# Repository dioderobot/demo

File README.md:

# Diode PCB boards

This repository contains schematics and boards built using the `pcb` command line utility by Diode, using the Zener language and open source compiler

## Prerequisites

For the most up to date information, visit our documentation at [`docs.pcb.new`](https://docs.pcb.new)

The open source PCB compiler is available at [`github.com/diodeinc/pcb`](https://github.com/diodeinc/pcb)

1. **KiCad 9.0**
   - Required for PCB layout
   - Download from [KiCad website](https://kicad.org/download)

## Project Structure

```
.
├── README.md
├── components              # Auto-generated component definitions (do not edit)
├── modules                 # User-authored reusable modules (.zen files)
├── boards                  # Board designs that use modules (.zen files)
└── pcb.toml               # Project configuration
```

## Usage Guidelines

### Building Projects
- Build your project using:
  ```bash
  pcb build
  ```

## Important Rules

1. **Dependencies**
   - Always use `pcb add` for dependencies
   - Never modify pcb.toml directly
   - Only add dependencies to directories with a `pcb.toml` file

2. **Best Practices**
   - Components in `components/` are auto-generated - never edit them manually
   - Create reusable modules in `modules/` directory
   - Board designs go in `boards/` directory
   - Use generic components for basic elements (capacitors, resistors, inductors)
   - Consult component datasheets when available

3. **Project Files**
   - Build artifacts are stored in `.pcb/` directory
   - Project configuration is in `pcb.toml`
   - Component files use `.zen` extension

## Zener Language Reference

Zener is a Starlark-based language for defining electronic components, modules, and boards as code. Starlark is a simplified dialect of Python designed for configuration files.

### Key Concepts

1. **Components** (in `components/` directory)
   - Auto-generated using `pcb search <PART_NUMBER>`
   - Never edit these manually
   - Stored as `.zen` files

2. **Modules** (in `modules/` directory)
   - User-authored reusable logic
   - Combine components and define connections
   - Named as `<module_name>.zen`

3. **Boards** (in `boards/` directory)
   - Instantiate modules for real-world use
   - Define the final PCB design
   - Named as `<board_name>.zen`

### Basic Syntax

Since Zener is based on Starlark, it follows Python-like syntax:
- Variables and functions follow Python conventions
- Comments use `#`
- Indentation matters
- No type annotations required

For detailed syntax and examples, refer to the [Diode PCB documentation](https://github.com/diodeinc/pcb)

## Component Management

Components are managed through the `pcb` command line tool:
- Use `pcb pro search <PART_NUMBER>` to find components
- Components are automatically downloaded and stored in `components/`
- Each component includes symbol, footprint, 3D model, and datasheet information

## Contributing

When contributing to this repository, please:
1. Follow the project structure
2. Use the provided tools for component and module creation
3. Ensure all components are properly documented
4. Test your changes with `pcb build`

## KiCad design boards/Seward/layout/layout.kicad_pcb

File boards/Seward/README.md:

# Seward

USB-C CMSIS-DAP v2 debug probe. STM32G0B1-based.

Drop-in replacement for a CMSIS-DAP v2 probe for flashing and debugging
Cortex-M targets. Target I/O rails auto-range over 1.8–5.0 V via
VTref-driven level shifters, so one probe covers every common target
voltage without jumpers or firmware switches. Exposes a keyed 10-pin
ARM Cortex-Debug header with bidirectional SWD and target-sourced SWO
capture presented to the host as a CDC-ACM virtual serial port.

## Highlights

- USB-C bus-powered, crystal-less (HSI48 + CRS), no PD negotiation
- STM32G0B1KBU6N (Cortex-M0+, UFQFPN-32 'N' pinout, 128 KB flash) —
  UCPD with internal dead-battery Rd, no external CC pulldowns
- Composite USB: CMSIS-DAP v2 (WinUSB, MS OS 2.0) + CDC-ACM for SWO;
  enumerates out of the box in `pyOCD` / `probe-rs` / `OpenOCD`
- Samtec FTSH-105 10-pin keyed ARM Cortex-Debug header (SWD + SWO)
- 1.8 V / 3.3 V / 5 V target support via 3× `SN74LXC1T45` level
  shifters driven by target VTref; firmware-controlled `SWD_DIR`
- nRESET driven directly from an FT_c (5 V tolerant) GPIO — no FET
  shifter, no body-diode back-feed path
- No probe-side back-feed when USB is unplugged (LXC1T45 Ioff + V₀₀
  disconnect, FT_c nRESET, no VTref buffer)
- Self-reflashable over USB DFU via BOOT0 button + USB cycle;
  Tag-Connect TC2030 SWD pads (unpopulated) for factory / recovery
- Three GPIO-driven status LEDs (STATUS green / DAP amber / SWO blue),
  no power-rail LED

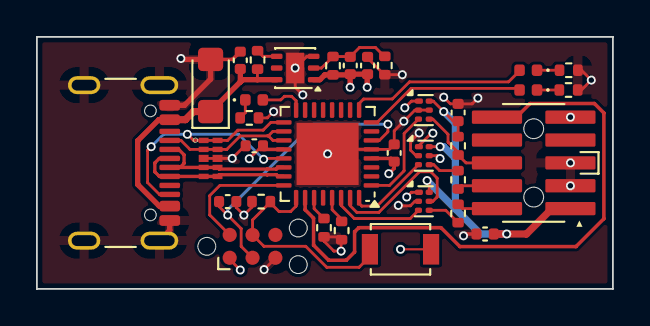
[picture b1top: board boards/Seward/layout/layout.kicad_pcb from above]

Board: 4 copper layers, 32.0 x 14.0 mm, 34 parts (0 on the bottom side), 31 nets.

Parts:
C1: GCM155R71H104KE02D; C_0402_1005Metric
C2, C3, C5, C6, C7, C8: GRM155Z71A105KE01D; C_0402_1005Metric
C4: GRM1555CYA103GE01D; C_0402_1005Metric
D1: LTST-C281KSKT; LED_0402_1005Metric
D2: VLMG1500-GS08; LED_0402_1005Metric
D3: VLMB1500-GS08; LED_0402_1005Metric
D4: SMF5V0A-E3; D_SMF
IC1: TPD4E05U06QDQARQ1; DQA_R-PUSON-N10_
J1: ?; Tag-Connect_TC2030-IDC-NL_2x03_P1.27mm_Vertical
J2: FTSH-105-01-L-DV-K-A-P-TR
J3: USB4105-GF-A; USB_C_Receptacle_GCT_USB4105-xx-A_16P_TopMnt_Horizontal
R1: ERJ-2RKF1002X; R_0402_1005Metric
R2, R3: ERJ-2RKF6800X; R_0402_1005Metric
R4, R5: ERJ-2RKF33R0X; R_0402_1005Metric
R6: ERJ-2RKF3300X; R_0402_1005Metric
R7, R8, R9, R10: ERJ-2RKF1003X; R_0402_1005Metric
R11: ERJ-2RKF5102X; R_0402_1005Metric
R12: ERJ-2RKF2553X; R_0402_1005Metric
SW1: B3U-1000P
U1: TPS74501PDRVR; TPS74x01P
U2, U3, U4: SN74LXC1T45DRYR; USON-6_1x1.45mm_P0.5mm
U5: STM32G0B1KBU6N; QFN-32-1EP_5x5mm_P0.5mm_EP3.45x3.45mm

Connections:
GND: C1.2, C2.2, C3.2, C5.2, C6.2, C7.2, C8.2, D4.2, IC1.3, IC1.8, J1.5, J2.3, J2.5, J2.9, J3.A1, J3.A12, J3.B1, J3.B12, J3.S1, R1.2, R2.2, R3.2, R6.2, R8.2, R9.2, R11.2, U1.3, U1.7, U2.2, U3.2, U4.2, U4.5, U5.5, U5.33
LED_DAP: D1.2, U5.8
LED_DAP_K: D1.1, R2.1
LED_STATUS: D2.2, U5.16
LED_STATUS_K: D2.1, R3.1
LED_SWO: D3.2, U5.9
LED_SWO_K: D3.1, R6.1
NRST: C1.1, J1.3, U5.6
SWD_A_SWCLK: U2.3, U5.32
SWD_A_SWDIO: U3.3, U5.30
SWD_B_SWCLK: J2.4, R4.2
SWD_B_SWDIO: J2.2, R5.2
SWD_DIR: U3.5, U5.31
SWD_LS_SWCLK: R4.1, U2.4
SWD_LS_SWDIO: R5.1, U3.4
SWD_SWCLK: J1.4, R1.1, SW1.1, U5.25
SWD_SWDIO: J1.2, U5.24
SWO_A: U4.3, U5.1
SWO_B: J2.6, R7.1, U4.4
TGT_NRESET: J2.10, U5.26
UCPD2_DBCC1: R8.1, U5.27
UCPD2_DBCC2: R9.1, U5.29
USB_C_CC1: IC1.2, IC1.9, J3.A5, U5.18, U5.19
USB_C_CC2: IC1.1, IC1.10, J3.B5, U5.17, U5.21
USB_C_D_N: IC1.4, IC1.7, J3.A7, J3.B7, U5.22
USB_C_D_P: IC1.5, IC1.6, J3.A6, J3.B6, U5.23
U_LDO.EN: R10.2, U1.4
U_LDO._FB: C4.2, R11.1, R12.2, U1.2
V3V3: C4.1, C6.1, C7.1, C8.1, J1.1, R12.1, SW1.2, U1.1, U2.1, U2.5, U3.1, U4.1, U5.4, U5.20
VBUS: C5.1, D4.1, J3.A4, J3.A9, J3.B4, J3.B9, R10.1, U1.6
VTREF: C2.1, C3.1, J2.1, R7.2, U2.6, U3.6, U4.6

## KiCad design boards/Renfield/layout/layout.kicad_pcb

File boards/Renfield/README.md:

# Renfield

USB-C PD sink dev board for STM32G0B1 UCPD firmware development.

The MCU runs the full PD sink stack itself — TCPP01-M12 is a
*protection* chip, not a PD controller. Plug into any USB-PD source,
negotiate a contract up to 20 V / 5 A, and pass the rail through a
firmware-gated OVP FET to a WAGO screw terminal.

## Highlights

- STM32G0B1KBU6N (Cortex-M0+, UFQFPN-32 'N' pinout, 128 KB flash)
- TCPP01-M12 + CSD17318Q2: hardware VBUS OVP @ 22 V, CC OVP @ 6 V,
  IEC 61000-4-2 L4 ESD on CC, connector-side dead-battery Rd
- Firmware-gated load rail (SSM3K15ACT shunt FET, default-off at
  reset) — firmware drives PA4 low to enable after PD contract
- Crystalless USB (HSI48 + CRS), USB-C data + CDC-ACM
- TPS70933 LDO from VBUS_RAW (always hot) → MCU survives OVP events
- WAGO 2060-452 push-in terminal for the negotiated rail
- Round Ø1.0 mm test pads: CC1/CC2 (connector-side, raw BMC), UART,
  scope trigger, OVP divider tap, GND
- Tag-Connect TC2030 SWD pads (no header populated — Cortex-M0+
  has no SWO)
- Four indicator LEDs (fault / contract / enum / heartbeat)

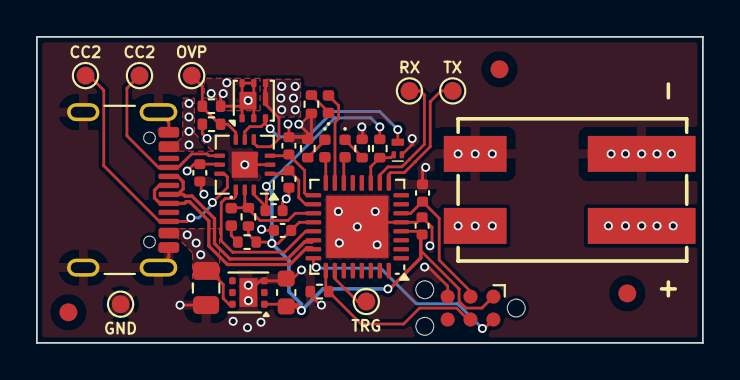
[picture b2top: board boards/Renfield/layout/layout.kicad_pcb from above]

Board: 4 copper layers, 37.0 x 17.0 mm, 41 parts (1 on the bottom side), 28 nets.

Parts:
C1, C2: GCM1555C1H221FA16D; C_0402_1005Metric
C3, C8, C9: GCM155R71H104KE02D; C_0402_1005Metric
C4: GRM21BZ71H475KE15K; C_0805_2012Metric
C5: GRM188Z71C475KE21D; C_0603_1608Metric
C6, C7: GRM155Z71A105KE01D; C_0402_1005Metric
D1: LTST-C281KSKT; LED_0402_1005Metric
D2, D4: VLMB1500-GS08; LED_0402_1005Metric
D3: VLMS1500-GS08; LED_0402_1005Metric
FID1, FID2, FID3: Fiducial; Fiducial_1mm_Mask2mm
J1: 2060-452/998-404; 2060-4xx_998-404-2P-white
J2: ?; Tag-Connect_TC2030-IDC-NL_2x03_P1.27mm_Vertical
J3: USB4105-GF-A; USB_C_Receptacle_GCT_USB4105-xx-A_16P_TopMnt_Horizontal
Q1: SSM3K15ACT,L3F; SSM3KxxxCT
Q2: CSD17318Q2; CSD1731xQ2
R1, R3: ERJ-2RKF1002X; R_0402_1005Metric
R2: ERJ-2RKF8200X; R_0402_1005Metric
R4, R6: ERJ-2RKF3900X; R_0402_1005Metric
R5: ERJ-2RKF4700X; R_0402_1005Metric
R7: ERJ-2RKF1003X; R_0402_1005Metric
R8: ERJ-2RKF1802X; R_0402_1005Metric
R9: ERJ-2RKF2943X; R_0402_1005Metric
TP1, TP2, TP3, TP4, TP5, TP6, TP7: ?; TestPoint_Pad_D1.0mm
U1: TPS70933QDRVRQ1; TPS709-Q1
U2: STM32G0B1KBU6N; QFN-32-1EP_5x5mm_P0.5mm_EP3.45x3.45mm
U3: TCPP01-M12; QFN-12-1EP_3x3mm_P0.5mm_EP1.45x1.45mm
V1: ?; version-footprint

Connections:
CC1_MCU: C1.1, U2.17, U3.3
CC2_MCU: C2.1, U2.18, U3.1
FET_GATE: Q1.3, Q2.3, U3.5
GND: C1.2, C2.2, C3.2, C4.2, C5.2, C6.2, C7.2, C8.2, C9.2, J1.2, J2.5, J3.A1, J3.A12, J3.B1, J3.B12, J3.S1, Q1.2, R1.2, R2.2, R4.2, R6.2, R8.2, TP3.1, U1.3, U1.7, U2.5, U2.33, U3.2, U3.13
HEARTBEAT_LED: D1.2, U2.15
LED_HEARTBEAT_K: D1.1, R2.1
LED_PD_CONTRACT_K: D2.1, R4.1
LED_TCPP01_FLT_A: D3.2, R5.2
LED_USB_ENUM_K: D4.1, R6.1
LOAD_EN_N: Q1.1, R3.2, U2.11
NRST: C3.1, J2.3, U2.6
OVP_SENSE: R8.1, R9.2, TP4.1, U3.6
PD_CONTRACT_LED: D2.2, U2.16
SCOPE_MARKER: TP5.1, U2.26
SWD_SWCLK: J2.4, R1.1, U2.25
SWD_SWDIO: J2.2, U2.24
TCPP01_DB: U2.21, U3.10
TCPP01_FLT: D3.1, R7.1, U2.19, U3.11
UART_RX: TP6.1, U2.10
UART_TX: TP7.1, U2.9
USB_C_CC1: J3.A5, TP1.1, U3.7
USB_C_CC2: J3.B5, TP2.1, U3.9
USB_C_D_N: J3.A7, J3.B7, U2.22
USB_C_D_P: J3.A6, J3.B6, U2.23
USB_ENUM_LED: D4.2, U2.14
V3V3: C5.1, C6.1, C7.1, C9.1, J2.1, R3.1, R5.1, R7.2, U1.1, U2.4, U2.20, U3.12
VBUS_PROT: J1.1, Q2.4, Q2.7, U3.4
VBUS_RAW: C4.1, C8.1, J3.A4, J3.A9, J3.B4, J3.B9, Q2.1, Q2.2, Q2.5, Q2.6, Q2.8, R9.1, U1.6, U3.8

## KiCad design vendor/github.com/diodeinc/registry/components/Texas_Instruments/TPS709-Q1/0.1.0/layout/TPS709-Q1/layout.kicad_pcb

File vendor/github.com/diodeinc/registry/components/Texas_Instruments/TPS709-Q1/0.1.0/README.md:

# TPS709-Q1 — TI 30 V, 150 mA low-Iq automotive LDO (WSON-6 / DRV)

Selector package for Texas Instruments' TPS709-Q1 AEC-Q100 linear
regulator family. All nine orderables share pinout, package, datasheet,
and performance — they differ only in the factory-trim output voltage.
Select by `output_voltage`; the matching silicon is picked automatically.

## Parts

| MPN | Vout | Max Dropout (150 mA) |
|-----|------|----------------------|
| TPS70912QDRVRQ1 | 1.2 V | — |
| TPS70915QDRVRQ1 | 1.5 V | — |
| TPS70918QDRVRQ1 | 1.8 V | — |
| TPS70925QDRVRQ1 | 2.5 V | — |
| TPS70927QDRVRQ1 | 2.7 V | — |
| TPS70928QDRVRQ1 | 2.8 V | — |
| TPS70930QDRVRQ1 | 3.0 V | 1.54 V |
| TPS70933QDRVRQ1 | 3.3 V | 1.54 V |
| TPS70950QDRVRQ1 | 5.0 V | 1.20 V |

All 9 share: 2.7–30 V Vin, 150 mA Iout, ~1 µA Iq, 80 dB PSRR at 10 Hz,
overcurrent / overtemperature / reverse-current / UVLO protection,
AEC-Q100 qualification.

## Selection

One config knob:

- `output_voltage` (Voltage) — factory-trim output. Must exactly match one
  of `"1.2V"`, `"1.5V"`, `"1.8V"`, `"2.5V"`, `"2.7V"`, `"2.8V"`, `"3V"`,
  `"3.3V"`, `"5V"`. Default: `"3.3V"`.

## Decoupling

Instantiated with the IC:

- `C_IN` — 4.7 µF / 50 V X7R / 0805. Sized for full 30 V Vin including
  automotive load-dump transients. Not required for stability per
  datasheet §7.1.1, but strongly recommended for ripple rejection.
- `C_OUT` — 4.7 µF / 16 V X7R / 0603. Meets the datasheet §7.1.1
  stability floor (≥ 2 µF effective for Vout < 1.5 V, ≥ 1.5 µF for
  Vout ≥ 1.5 V) across all 9 trims after tolerance + DC-bias derating.

## EN

Exposed as an optional `io(Net, ...)` with a default `NotConnected()` —
the datasheet explicitly allows EN to float (internal pull-up enables the
device). If driving externally, keep V_EN ≤ 6.5 V — do not tie EN to VIN
if VIN can exceed 6.5 V.

## Example

```zen
TPS709_Q1 = Module("@github/diodeinc/registry/components/Texas_Instruments/TPS709-Q1/TPS709-Q1.zen")

# Default 3.3 V (TPS70933QDRVRQ1)
TPS709_Q1(name="U_3V3", VIN=VBAT, VOUT=V3V3, GND=GND)

# Explicit 5 V rail, EN driven by an MCU GPIO (must be ≤ 6.5 V)
TPS709_Q1(
    name="U_5V",
    output_voltage="5V",
    VIN=VBAT,
    VOUT=V5,
    GND=GND,
    EN=SYS_EN,
)
```

## Package

**DRV / WSON-6** — 2 × 2 × 0.8 mm, 6-pin leadless DFN with exposed thermal
pad. Footprint is KiCad's stock `WSON-6-1EP_2x2mm_P0.65mm_EP1x1.6mm`
(IPC-7351 nominal density); electrically equivalent to TI's recommended
DRV land pattern. STEP 3D model is the KiCad-bundled file, embedded in
the `.kicad_mod` for self-contained use.

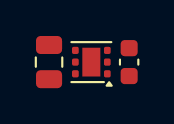
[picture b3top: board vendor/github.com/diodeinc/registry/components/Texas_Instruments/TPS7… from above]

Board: 2 copper layers, 3 parts (0 on the bottom side), 3 nets, no tracks yet.

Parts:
C1: GRM21BZ71H475KE15K; C_0805_2012Metric
C2: GRM188Z71C475KE21D; C_0603_1608Metric
U1: TPS70933QDRVRQ1; TPS709-Q1

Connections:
GND: C1.2, C2.2, U1.3, U1.7
VIN: C1.1, U1.6
VOUT: C2.1, U1.1

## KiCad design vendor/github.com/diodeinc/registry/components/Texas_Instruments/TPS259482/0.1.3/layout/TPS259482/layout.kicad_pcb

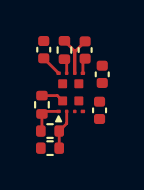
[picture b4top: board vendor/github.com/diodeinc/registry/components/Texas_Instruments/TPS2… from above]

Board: 2 copper layers, 9 parts (0 on the bottom side), 8 nets.

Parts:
C1: GCM1555C1H102FA16D; C_0402_1005Metric
C2, C4: GCM155R71H104KE02D; C_0402_1005Metric
C3: GRM1555CYA103GE01D; C_0402_1005Metric
R1: ERJ-2RKF3923X; R_0402_1005Metric
R2: ERJ-2RKF2672X; R_0402_1005Metric
R3: ERJ-2RKF7152X; R_0402_1005Metric
R4: ERJ-2RKF9760X; R_0402_1005Metric
U1: TPS259482AYWPR; TPS259482

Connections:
DVDT: C1.1, U1.7
EN: R1.2, R3.1, U1.1
GND: C1.2, C2.2, C3.2, C4.2, R2.2, R4.2, U1.8
ILM_MON: R4.1, U1.9
ITIMER: C3.1, U1.10
OVLO: R2.1, R3.2, U1.2
VIN: C2.1, R1.1, U1.5, U1.12
VOUT: C4.1, U1.6, U1.11

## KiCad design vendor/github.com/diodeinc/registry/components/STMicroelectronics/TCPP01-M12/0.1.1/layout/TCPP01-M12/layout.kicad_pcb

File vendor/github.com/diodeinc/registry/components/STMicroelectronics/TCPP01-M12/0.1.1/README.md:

# TCPP01-M12

STMicroelectronics USB Type-C port protection IC for sink applications. Provides
ESD, short-to-VBUS OVP on CC1/CC2, programmable VBUS OVP via an external
N-MOSFET, dead-battery management, and open-drain fault reporting in a 3 × 3 mm
QFN-12L.

The package ships a minimal reference circuit around the IC (VCC decoupling,
IN_GD ESD shunt, VBUS_CTRL divider, FLT pull-up). Use-case-specific parts
(external N-MOSFET, DB/ network, CC EMI caps, VBUS bulk/TVS) are still the
integrator's responsibility — see the `.zen` docstring.

## Usage

```python
TCPP01_M12 = Module("@github/diodeinc/registry/components/STMicroelectronics/TCPP01-M12/TCPP01-M12.zen")

TCPP01_M12(
    name="U1",
    VCC=vcc_3v3,
    GND=gnd,
    # Connector side
    CC1C=usb_cc1,
    CC2C=usb_cc2,
    IN_GD=usb_vbus,
    # System side
    CC1=mcu_cc1,
    CC2=mcu_cc2,
    SOURCE=sys_vbus,
    GATE=fet_gate,
    VBUS_CTRL=ovp_set,
    DB=dead_batt,
    FLT=fault_n,
    # Optional: override VBUS OVP trip (default 22 V for full PD range).
    # Use ~6 V for 5 V-only sinks.
    # vbus_ovp_threshold=Voltage("6V"),
)
```

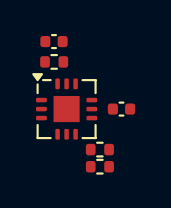
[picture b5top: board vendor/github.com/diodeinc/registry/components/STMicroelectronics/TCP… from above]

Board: 2 copper layers, 6 parts (0 on the bottom side), 5 nets, no tracks yet.

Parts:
C1, C2: GCM155R71H104KE02D; C_0402_1005Metric
R1: ERJ-2RKF1003X; R_0402_1005Metric
R2: ERJ-2RKF1802X; R_0402_1005Metric
R3: ERJ-2RKF2943X; R_0402_1005Metric
U1: TCPP01-M12; QFN-12-1EP_3x3mm_P0.5mm_EP1.45x1.45mm

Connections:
FLT: R1.1, U1.11
GND: C1.2, C2.2, R2.2, U1.2, U1.13
IN_GD: C1.1, R3.1, U1.8
VBUS_CTRL: R2.1, R3.2, U1.6
VCC: C2.1, R1.2, U1.12

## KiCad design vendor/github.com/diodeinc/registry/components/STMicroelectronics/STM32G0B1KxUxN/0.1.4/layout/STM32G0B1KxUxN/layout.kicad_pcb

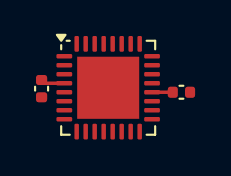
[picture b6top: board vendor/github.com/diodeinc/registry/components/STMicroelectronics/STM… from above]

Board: 2 copper layers, 3 parts (0 on the bottom side), 2 nets.

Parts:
C1, C2: GRM155Z71A105KE01D; C_0402_1005Metric
U1: STM32G0B1KCU6N; QFN-32-1EP_5x5mm_P0.5mm_EP3.45x3.45mm

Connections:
GND: C1.2, C2.2, U1.5, U1.33
VDD: C1.1, C2.1, U1.4, U1.20

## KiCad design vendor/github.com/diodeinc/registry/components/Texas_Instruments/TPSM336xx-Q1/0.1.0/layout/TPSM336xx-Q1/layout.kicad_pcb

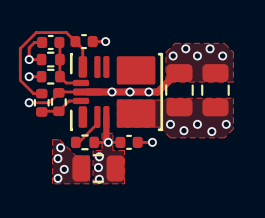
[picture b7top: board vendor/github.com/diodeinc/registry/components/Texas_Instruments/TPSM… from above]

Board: 2 copper layers, 12 parts (0 on the bottom side), 7 nets.

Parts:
C1: GCM1555C1H100FA16D; C_0402_1005Metric
C2: GRM21BZ71H475KE15K; C_0805_2012Metric
C3: GCM155R71H104KE02D; C_0402_1005Metric
C4, C5: GRM21BZ71A226ME15K; C_0805_2012Metric
C6: GRM155Z71A105KE01D; C_0402_1005Metric
R1, R4, R5: ERJ-2RKF1003X; R_0402_1005Metric
R2: ERJ-2RKF1002X; R_0402_1005Metric
R3: ERJ-2GE0R00X; R_0402_1005Metric
U1: TPSM33620S3QRDNRQ1; TPSM336xx-Q1

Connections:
EN: R1.2, U1.2
FB: C1.2, R2.1, R3.2, U1.9
GND: C2.2, C3.2, C4.2, C5.2, C6.2, R2.2, R4.2, U1.10
MODE_SYNC: R4.1, R5.2, U1.11
VCC: C6.1, R5.1, U1.8
VIN: C2.1, C3.1, R1.1, U1.3
VOUT: C1.1, C4.1, C5.1, R3.1, U1.4

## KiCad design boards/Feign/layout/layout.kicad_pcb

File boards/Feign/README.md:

# Feign

USB-C to 3.3 V UART bridge. STM32G0B1-based.

Enumerates over USB as a standard CDC-ACM virtual serial port. An
optional firmware build emulates the FTDI UART-mode protocol for
`pyftdi` / `libftdi` compatibility.

## Highlights

- USB-C bus-powered, crystal-less (HSI48 + CRS), no PD negotiation
- STM32G0B1 (Cortex-M0+, UFQFPN-32 'N' pinout) — UCPD with internal
  dead-battery Rd, no external CC pulldowns required
- 1×6 SMD right-angle header, SparkFun FTDI Basic pinout:
  `GND · CTS · VCC · TXD · RXD · DTR`
- 5 V VCC pin to target, current-limited to ~400 mA with auto-retry
  (TPS2553) and firmware enable + fault flag
- 3.3 V CMOS UART signals; RX and CTS routed to FT_c pins so they
  tolerate 5 V from an externally-powered target while Feign is unpowered
- BOOT0 + RESET tactile buttons, Tag-Connect TC2030 SWD pads
- Three indicator LEDs (power / TX / RX), brightness-equalised

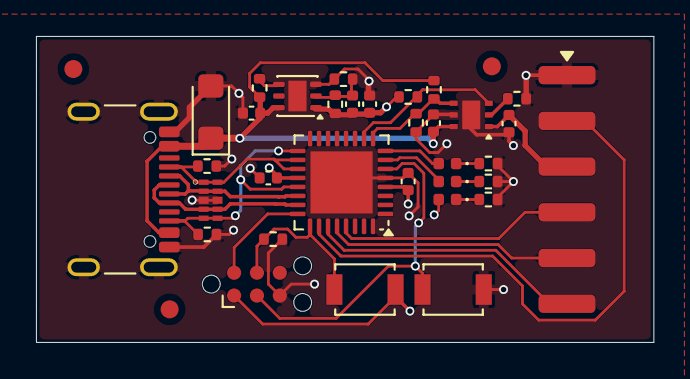
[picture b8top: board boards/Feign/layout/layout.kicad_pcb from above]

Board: 4 copper layers, 34.3 x 17.0 mm, 37 parts (1 on the bottom side), 25 nets.

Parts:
C1: GRM1555CYA103GE01D; C_0402_1005Metric
C2, C3, C4, C5, C6, C7: GRM155Z71A105KE01D; C_0402_1005Metric
D1: VLMG1500-GS08; LED_0402_1005Metric
D2: VLMB1500-GS08; LED_0402_1005Metric
D3: LTST-C281KSKT; LED_0402_1005Metric
D4: SMF5V0A-E3; D_SMF
FID1, FID2, FID3: Fiducial; Fiducial_1mm_Mask2mm
IC1: TPD4E05U06QDQARQ1; DQA_R-PUSON-N10_
J1: M20-8890645R; M20-8890645
J2: ?; Tag-Connect_TC2030-IDC-NL_2x03_P1.27mm_Vertical
J3: USB4105-GF-A; USB_C_Receptacle_GCT_USB4105-xx-A_16P_TopMnt_Horizontal
R1, R2: ERJ-2RKF5101X; R_0402_1005Metric
R3: ERJ-2RKF1002X; R_0402_1005Metric
R4: ERJ-2RKF2200X; R_0402_1005Metric
R5: ERJ-2RKF3900X; R_0402_1005Metric
R6: ERJ-2RKF8200X; R_0402_1005Metric
R7, R8, R9, R12: ERJ-2RKF1003X; R_0402_1005Metric
R10: ERJ-2RKF5102X; R_0402_1005Metric
R11: ERJ-2RKF2553X; R_0402_1005Metric
R13: ERJ-2RKF6492X; R_0402_1005Metric
SW1, SW2: B3U-1000P
U1: TPS74501PDRVR; TPS74x01P
U2: STM32G0B1KBU6N; QFN-32-1EP_5x5mm_P0.5mm_EP3.45x3.45mm
U3: TPS2553DRVR; TPS2553DRV
V1: ?; version-footprint

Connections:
GND: C2.2, C3.2, C4.2, C5.2, C6.2, C7.2, D4.2, IC1.3, IC1.8, J1.1, J2.5, J3.A1, J3.A12, J3.B1, J3.B12, J3.S1, R1.2, R2.2, R3.2, R4.2, R5.2, R6.2, R7.2, R10.2, R13.2, SW2.2, U1.3, U1.7, U2.5, U2.33, U3.5, U3.7
LED_PWR_K: D1.1, R4.1
LED_RX: D2.2, U2.8
LED_RX_K: D2.1, R5.1
LED_TX: D3.2, U2.7
LED_TX_K: D3.1, R6.1
MODEM_CTS: J1.2, U2.26
MODEM_DTR: J1.6, U2.27
NRST: J2.3, SW2.1, U2.6
SWD_SWCLK: J2.4, R3.1, SW1.1, U2.25
SWD_SWDIO: J2.2, U2.24
UART_RX: J1.5, U2.28
UART_TX: J1.4, U2.29
USB_C_CC1: IC1.1, IC1.10, J3.A5, R1.1, U2.18, U2.19
USB_C_CC2: IC1.5, IC1.6, J3.B5, R2.1, U2.17, U2.21
USB_C_D_N: IC1.2, IC1.9, J3.A7, J3.B7, U2.22
USB_C_D_P: IC1.4, IC1.7, J3.A6, J3.B6, U2.23
U_LDO.EN: R9.2, U1.4
U_LDO._FB: C1.2, R10.1, R11.2, U1.2
U_VCC_SW._ILIM: R13.1, U3.2
V3V3: C1.1, C3.1, C4.1, C5.1, D1.2, J2.1, R8.2, R11.1, SW1.2, U1.1, U2.4, U2.20
VBUS: C2.1, C6.1, D4.1, J3.A4, J3.A9, J3.B4, J3.B9, R9.1, R12.2, U1.6, U3.6
VCC_EN: R7.1, R12.1, U2.9, U3.4
VCC_FAULT: R8.1, U2.10, U3.3
VCC_OUT: C7.1, J1.3, U3.1

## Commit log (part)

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2025-08-29 regenerate
2025-09-08 Update GitHub workflow: pcb-release.yml (#1)
2025-09-15 Fix cyclical dependencies
2025-09-16 Add DM0002
2025-09-16 Include DB0002 layout files
2025-09-21 Update GitHub workflow: pcb-release.yml (#14)
2025-09-25 Remove unnecessary .gitkeep
2025-10-08 Update GitHub workflow: pcb-release.yml (#20)
2025-10-10 Use debian 13 kicad image
2025-10-16 Bump stdlib, add auto impedance matching
2025-10-20 update stdlib
2025-10-31 add fw
2025-10-31 add a bringup script
2025-11-10 Remove config_properties
2025-11-11 Update GitHub workflow: pcb-release.yml (#27)
2025-11-13 Use new PhysicalValue APIs
2025-11-15 Update GitHub workflow: pcb-release.yml (#28)
2025-11-18 Use generic BOM matching for LEDs
2025-11-25 Use value instead of resistance for ferrite bead
2025-12-04 Bump CI pcb version
2025-12-04 Use new pcb info (#31)
2025-12-10 add cm5 carrier
2025-12-10 fix mounting holes
2025-12-10 skip bom pos
2025-12-10 vendored
2025-12-10 add logging
2025-12-10 Update DM0002 graphics
2025-12-10 match more components
2025-12-11 pass drc no unconnected nets + bom matched
2025-12-17 Update GitHub workflow: pcb-release.yml (#40)
2026-01-07 Use stdlib PinHeader
2026-01-10 Update GitHub workflows (#43)
2026-01-15 Add AM32-Embassy: Rust ESC firmware using Embassy framework
    Initial implementation of AM32 ESC firmware in Rust for DM0001:
    Core modules:
    - motor/commutation.rs: 6-step commutation table
    - motor/pwm.rs: TIM1 PWM driver structure (placeholder)
    - motor/bemf.rs: ADC-based BEMF zero-crossing detection
    - motor/startup.rs: Open-loop startup sequence
2026-01-15 Complete AM32-Embassy implementation with all core modules (#47)
    Added:
    - drivers/adc.rs: ADC sensing for voltage, current, temperature
    - drivers/input_capture.rs: DSHOT/PWM input capture driver
    - drivers/can.rs: CAN bus message structures and commands
    - drivers/telemetry.rs: Telemetry output (DSHOT, KISS protocols)
    - motor/controller.rs: Full motor control state machine
2026-01-16 Update fp-lib-table to use stable paths
2026-01-21 Update GitHub workflows (#49)
2026-01-23 Update GitHub workflows (#52)
2026-01-26 Test new publish flow
2026-02-12 Update GitHub workflows (#57)
2026-02-13 Bump stdlib, run `pcb fmt` (#58)
    * Delete unused Crystal.zen
    * Bump stdlib
    * Run pcb fmt
2026-02-13 Don't vendor all of AM32
    It has a ton of bloat
2026-02-13 Use `schematic=`
2026-02-13 Remove unused config_properties
2026-02-13 Remove test file
2026-02-13 Remove stale properties
2026-02-16 Update GitHub workflows (#63)
2026-03-02 Update GitHub workflows (#65)
2026-03-04 Replace assets with regular dependencies
2026-03-04 adding LMV321 for use as a unity gain buffer'
2026-03-04 changed to a unity gain opamo with better protection from itsself being backpowered
2026-03-05 adding unplaced bypass cap in case something is wrong with the buffer circuit
2026-03-05 added level shifters in case target is on non-3V3 power rail
2026-03-05 board outline expanded a couple mm, level shifters added. committing before further adjusting GPIO assignments
2026-03-05 samtec SMT connector added to components
2026-03-05 updates to component 3D model
2026-03-05 fixed level shift voltage violation in schematic
2026-03-06 resest level shifter added to schematic
2026-03-06 lots of DRCs were being ignored based on kicad setting, committing changes before editing board config setup with MFG constraints from Nasheed based on planned manufacter for these PCBs
2026-03-06 add LevelShiftFet as explicit dependency to fix CI build
    Made-with: Cursor
2026-03-07 better bringup instructions
2026-03-09 feat(TXB0102DCUR): add correct VSSOP-8 footprint with 0.5mm pitch
    The TXB0102DCUR uses a VSSOP-8 package with 0.5mm pitch, not 0.65mm.
    Created new footprint with correct pad positions and naming convention.
    Made-with: Cursor
2026-03-09 chore(DM0002): update PCB layout
    Made-with: Cursor
2026-03-09 chore(DM0002): set panel metadata DM0002 v4.0.0 ba4961b
    Made-with: Cursor
2026-03-21 chore(DM0001): update layout
2026-03-23 fix(DM0003): replace local CRJ009-ML4-TH with registry version
    Switch Ethernet connector from local components/Same_Sky/CRJ009-ML4-TH
    to github.com/diodeinc/registry/components/SkyMirr/CRJ009-ML4-TH@0.1.0.
    Pin names changed: TRD{0-3}P/M → TRD{0-3}_POS/_NEG.
    Deleted local component package (symbol, footprint, datasheet, zen).
    Diode-Thread: https://app.diode.computer/pcb-ai-sessions/9cfef096-87fc-424a-bd2a-e2490d9a95a6
2026-03-24 Remove unused dependency
2026-04-11 Bump dependencies
2026-04-13 Tune DM0001 bringup motor-control profiles
2026-04-14 Capture working DM0001 ST MCSDK bringup
2026-04-14 Vendor recovered DM0001 ST controller baseline
2026-04-19 fix(DM0002): resolve all build warnings
    - Migrate deprecated io() default= to template-first form in
    Oscillator.zen and USB4105.zen
    - Remove explicit no_connect pin wiring in TLV758P.zen (DNC pin)
    - Fix power pin types: Net -> Power/Ground on LMV321IDBVR,
    TLV9001IDBVR, TXB0102DCUR component packages
    - Replace deprecated Gpio(NET=) and Analog(NET=) with positional
2026-04-19 fix(DM0003): resolve all build warnings
    - Fix power pin types: Net -> Power/Ground on TYPE-C24PQT, TUSB321RWBR,
    STMPS2151STR, LIS3DH, SN74LVC1G14DRLRG4 component packages
    - Remove explicit no_connect pin wiring from component packages
    (1M2199119M3, AP3441SHEM7B, AP3441LSHEM7B, MKM11C04MG013, LIS3DH,
    SN74LVC1G14DRLRG4) and call sites (AP3441x, LIS3DH ref, PCIe-M2,
    IO, DM0003)
2026-04-19 fix(USB4105): restore SHIELD default to GND
    The template-first io() migration created an independent Ground
    for SHIELD when omitted, leaving the USB-C shell floating.
2026-04-19 chore: fix -Wstyle lints
    Remove redundant first-arg names from io(), config(), Net(), Power(),
    and Ground() calls where the name matches the LHS binding, and rename
    lowercase io() bindings to uppercase to match their public names.
2026-04-27 feat(Feign): scaffold DM0004 USB-C to UART bridge
    STM32G0B1-based FTDI clone (UART mode). Adds boards/Feign/ scaffolding
    and design spec covering:
    - UsbCSink16P module front-end (CC Rd DNP, UCPD dead-battery used instead)
    - TPS745x ULDO 3V3 with PG-driven power LED
    - TPS2553DRVR load switch on 5V VCC_OUT (auto-retry, 500 mA)
    - 1x6 SMD right-angle header (Harwin M20-8890645), SparkFun FTDI Basic pinout
2026-04-27 fix(Feign): address EE review findings
    Two critical schematic issues from EE review:
    1. UCPD dead-battery: AN5225 §11.3.1 requires DBCCx shorted to CCx for
    the internal Rd to expose itself when V_DD=0. Wire PA9→PA8 and
    PA10→PB15 (single-net per CC). PA9/PA10 are now reserved.
    2. 5 V-tolerant inputs: only PA8, PB15, PD0, PD2 are FT_c on the 32-pin
    'N' package. PA8/PB15 are taken by CC1/CC2, so user-facing inputs
2026-04-27 layout(Feign): initial 4-layer board layout
    - TC2030-NL (no-legs) variant for SWD pads
    - 2 \u2192 4 layer stackup
2026-04-27 feat(Feign): add silkscreen version stamp and Diode logo
2026-04-29 Fix DM0003 layout error
2026-04-29 fix(Renfield): swap VBUS gate FET to CSD17318Q2 (2x2 WSON-6)
    TCPP01-M12 datasheet (DS12900 Rev 7, Table 6) confirms VGS is internally
    regulated to typ 5.5 V (5.0-6.0 V max) regardless of VBUS level. With
    the gate held at ~5.5 V, the original CSD17578Q3A's 5.6 mOhm-at-4.5V
    spec is overkill for this board's 5 A continuous design point; we don't
    need the 3x3 SON-8 footprint.
    CSD17318Q2 (2x2 WSON-6) is 25 A rated, ~20 mOhm at TCPP01's regulated
2026-04-30 Add STM32G0B1 PD controller board spec (#82)
    * feat(Renfield): add design spec for STM32G0B1 USB-PD sink dev board
    Pre-capture documentation for DM0005 (Renfield), a USB-C PD sink
    development board built around the STM32G0B1 UCPD peripheral. Design
    optimized for firmware development on the PD sink stack: full
    observability via probe headers, addressable LED bargraphs for live
    V/I telemetry, hardware OVP backstop, latch-off load eFuse, and 8-pos
2026-05-01 feat(Renfield): scaffold board with PD power-input core
    USB-C \u2192 TCPP01-M12 \u2192 CSD17318Q2 N-FET \u2192 VBUS_PROT, plus the STM32G0B1
    UCPD1 wiring (PA8/PB15 = CC1/CC2; PA9/PA10 = DBCC dead-battery sense
    shorted to PA8/PB15 per AN5225 \u00a711.3.1). Hardware OVP fixed at ~22 V
    typical via 165 k / 10 k VBUS_CTRL divider (range 21.0\u201323.45 V over
    the 1.20\u20131.34 V threshold spec).
    Includes:
2026-05-01 refactor(Renfield): tie TCPP01 VCC straight to V3V3
    Renfield is USB-only \u2014 no battery, no 0-Iq standby benefit. The
    GPIO-as-VCC trick (DS12900 \u00a76.7) only buys quiescent-current savings
    on battery-powered sinks; here it just costs a GPIO and adds a
    firmware step at boot.
    Net effect:
    - TCPP01 VCC now sourced directly from V3V3; chip powers up the
2026-05-02 feat(Renfield): add NFET shunt on eFuse EN/UVLO for firmware kill switch
    Addresses EE review finding: wiring a push-pull GPIO directly to the
    TPS259482 EN/UVLO analog divider node clamps OVLO's sense voltage to
    3.3 V \u00d7 R_LOW/(R_MID+R_LOW) \u2248 0.67 V, below the 1.2 V trip threshold
    \u2014 defeating the 22 V hardware OVLO for any input voltage.
    Fix (on-board, not in the registry ref design):
    - CSD13380F3 FemtoFET (N-channel 12V, 76 m\u03a9, PICOSTAR YJM): drain on
2026-05-02 feat(Renfield): add 5 remaining status LEDs
    Completes the 7-LED status array per spec \u00a75:
    Hardware-driven fault LEDs (V3V3 -> R -> LED -> open-drain pin):
    - TCPP01_FLT (red) - 470 ohm, ~3 mA, ~6 mcd
    - EFUSE_FLT (red) - 470 ohm, ~3 mA, ~6 mcd
    Light when the respective fault pin pulls low; survive MCU crash
    because they're independent of firmware.
2026-05-02 feat(Renfield): add 2x4 PD-dev probe header (R12)
    Single 2x4 SMT vertical 2.54 mm male header (stdlib generic; resolves
    to Wurth 61000821121) replacing the two 2x4 grommet-compatible headers
    in the original spec. Hookup-wire breakout to Saleae instead of the
    grommet fitting lets us drop the strict signal/GND alternation and
    pack all 6 PD-dev-relevant signals + 2 GND on one header.
    Pin map:
2026-05-02 docs(Renfield): clean up spec to match implementation; trim low-level detail
    Two goals:
    1. Remove drift: the .zen now has probe headers, test pads, LEDs, and
    support passives that the old spec no longer matched.
    2. Raise the abstraction level: the spec should answer 'what' and
    'why', not 'which 1% E96 resistor'. That's the .zen's job.
    Changes:
2026-05-03 layout(Renfield): finalize pinout for routing + swap buck to TPS709 LDO
    Pinout tweaks for easier layout:
    - TCPP01 FLT\u2192PA9, DB\u2192PA10 (reclaimed DBCC pins, short routes to TCPP01)
    - Status LEDs moved to PB0/PB1/PA7 (closer to LED cluster)
    - SCOPE_MARKER moved to PD0 (TIM16_CH1, frees PA6)
    - CC1/CC2 swapped on TCPP01\u2192MCU side (saves a trace crossing)
    - DBCC1/DBCC2 dropped; firmware releases G0 internal Rd via
2026-05-04 layout(Renfield): layout tweaks + bump Logo to 0.5.1
2026-05-04 docs(Renfield): sync spec with kill-FET + tighten
    - Add R6 (firmware-gated load rail at reset), renumber R7\u2013R12.
    - Update \u00a73 diagram to show Q_KILL on the main FET gate.
    - Rewrite \u00a74 boot sequence for firmware-gated enable ordering.
    - Fix LED prose in \u00a75: non-fault LEDs are active-high source-driven,
    not pull-up-sink (reviewer \u00a75.4).
    - Add design note #3 for Q_KILL; tweak note #2 to acknowledge the
2026-05-04 feat(Seward): implement core board, stdlib interfaces, UCPD2 guards
    Core STM32G0B1 circuitry:
    - USB-C receptacle (UsbC16P) + TPD4E05U06 ESD (D+/D-/CC)
    - TPS74501P 3V3 LDO off VBUS
    - MCU with UCPD1 dead-battery (DBCC shorted to CC), USB FS, self-SWD,
    Tag-Connect recovery, BOOT0/NRST buttons, 4 activity LEDs
    - Swd()/Uart() interfaces for the A-side of the pending target level
2026-05-05 chore(Seward): clean up stale comments and duplication
    - .zen: trim verbose comments, fix stale net-label pin references
    (PA4/PA5/PA6 \u2192 PB6/PB7/PB8), drop layout detail that duplicates
    spec \u00a75, remove redundant ARM header pinout comment.
    - spec: remove stale VBUS bulk-cap and SMAJ5.0A mentions, correct
    LS count (4\u21923), fix duplicate LS table row, fix DS13557\u2192DS13560
    datasheet reference, update SWD_DIR idle pin (PB6\u2192PB7), prune
